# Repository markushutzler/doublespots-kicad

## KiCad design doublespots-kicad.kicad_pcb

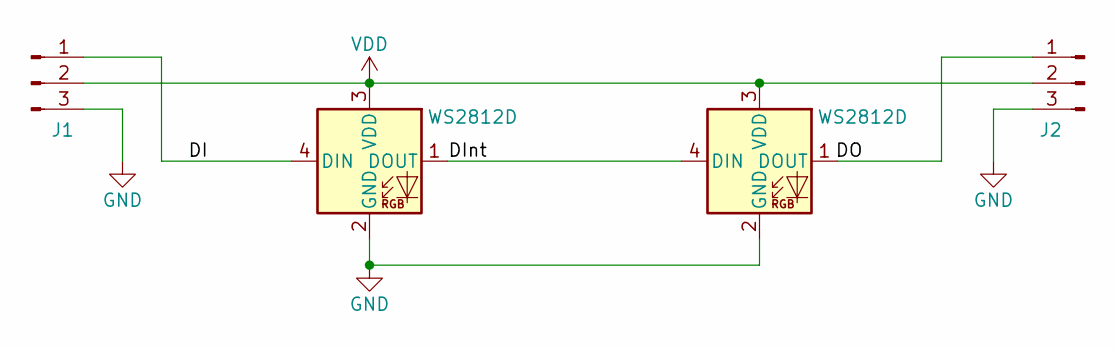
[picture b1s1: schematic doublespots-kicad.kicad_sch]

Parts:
J1, J2: Conn_01x03_Pin; con_1x03_solder
LED1, LED2: WS2812D; LED_D4.74mm-4_RGB

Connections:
/DI: J1.1, LED1.4 (DIN)
/DInt: LED1.1 (DOUT), LED2.4 (DIN)
/DO: J2.1, LED2.1 (DOUT)
GND: J1.3, J2.3, LED1.2 (GND), LED2.2 (GND)
VDD: J1.2, J2.2, LED1.3 (VDD), LED2.3 (VDD)

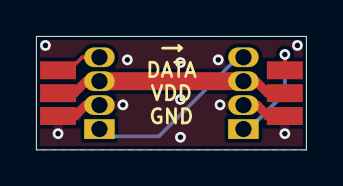
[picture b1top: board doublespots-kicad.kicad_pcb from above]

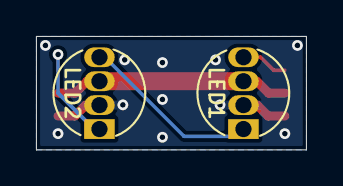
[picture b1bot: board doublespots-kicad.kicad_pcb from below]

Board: 2 copper layers, 15.0 x 6.3 mm, 4 parts (2 on the bottom side), 5 nets.

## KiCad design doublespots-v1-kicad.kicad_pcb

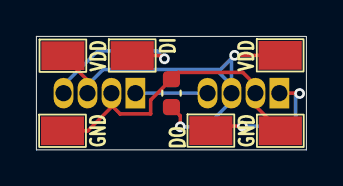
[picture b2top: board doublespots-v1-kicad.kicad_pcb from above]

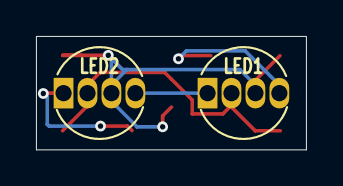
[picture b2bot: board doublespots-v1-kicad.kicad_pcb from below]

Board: 2 copper layers, 15.0 x 6.3 mm, 9 parts (2 on the bottom side), 5 nets.

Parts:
C1: 100nf; C_0603_1608Metric
DI: DI; TestPoint_Pad_2.4x1.6mm
DO: DO; TestPoint_Pad_2.4x1.6mm
GND: GND; TestPoint_Pad_2.4x1.6mm
GND#2: GND; TestPoint_Pad_2.4x1.6mm
LED1, LED2: WS2812D; LED_D4.74mm-4_RGB
VDD: VDD; TestPoint_Pad_2.4x1.6mm
VDD#2: VDD; TestPoint_Pad_2.4x1.6mm

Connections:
/DI: DI.1, LED1.4 (DIN)
/DInt: LED1.1 (DOUT), LED2.4 (DIN)
/DO: DO.1, LED2.1 (DOUT)
/GND: C1.2, GND.1, GND#2.1, LED1.2 (GND), LED2.2 (GND)
/VDD: C1.1, LED1.3 (VDD), LED2.3 (VDD), VDD.1, VDD#2.1

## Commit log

2025-10-21 needed a via and not so nice routing... but no more errors
2025-10-22 Update PCB with connectors and ground plane
    This change also adds a ground plane and reworks some routing.
